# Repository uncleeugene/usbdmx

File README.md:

# usbdmx
Galvanically isolated clone of Enttec USB-DMX

Notice: "main" branch contains USB-B version of the board. In "usbc" branch there is USB-C version, but it is not done yet!

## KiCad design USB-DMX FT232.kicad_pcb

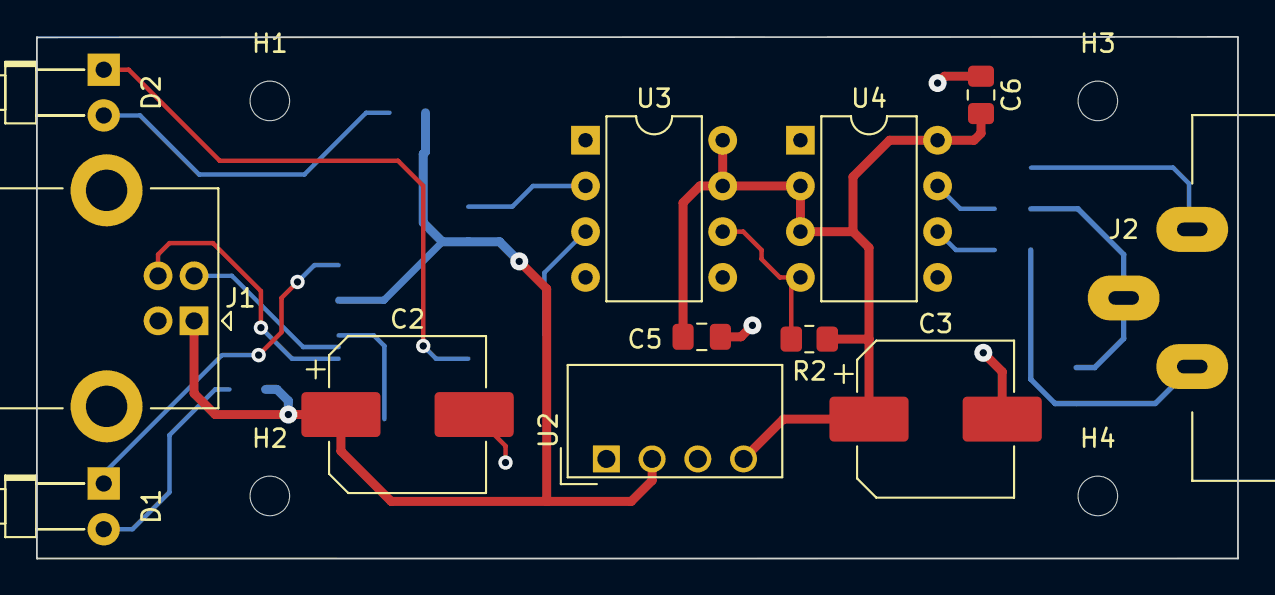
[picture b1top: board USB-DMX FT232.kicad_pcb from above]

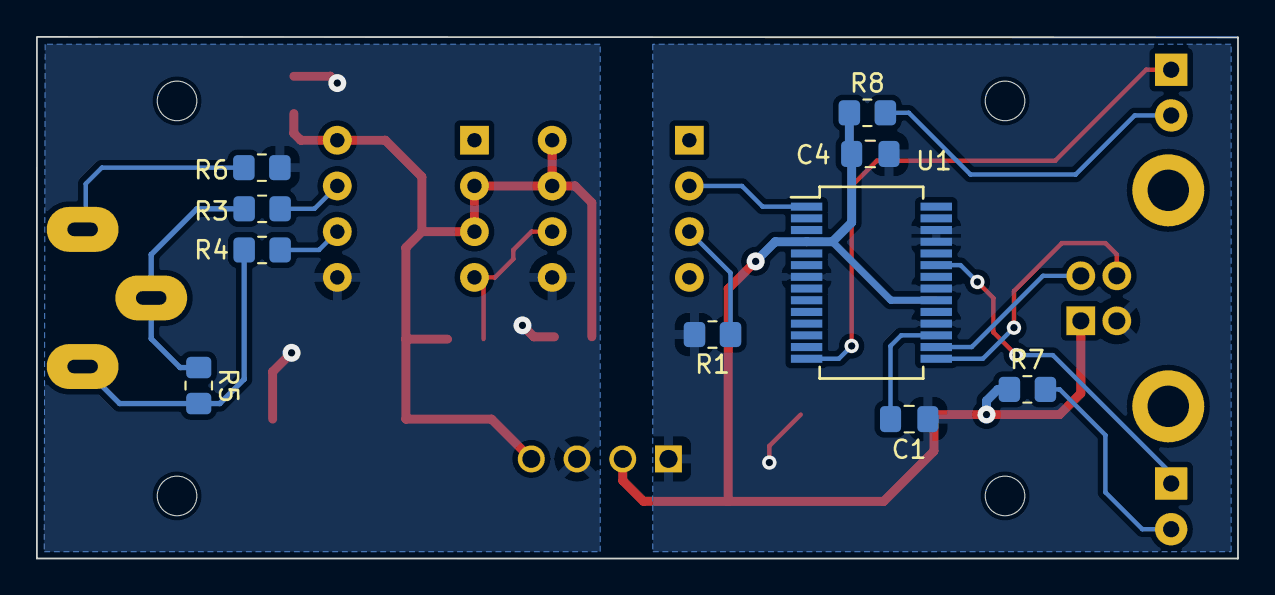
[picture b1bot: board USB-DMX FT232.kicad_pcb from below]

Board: 2 copper layers, 66.7 x 29.0 mm, 26 parts (10 on the bottom side), 19 nets.

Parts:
C1: 100nF; C_0805_2012Metric_Pad1.18x1.45mm_HandSolder
C2, C3: 100uF; CP_Elec_8x10.5
C4, C5, C6: 10nF; C_0805_2012Metric_Pad1.18x1.45mm_HandSolder
D1, D2: LED; LED_D1.8mm_W1.8mm_H2.4mm_Horizontal_O3.81mm_Z1.6mm
H1, H2, H3, H4: MountingHole_Pad; MountingHole_2.2mm_M2
J1: USB; USB_B_Lumberg_2411_02_Horizontal
J2: NC3MAFH-PH; XLR 3pin Female Angle
R1: 1K; R_0805_2012Metric_Pad1.20x1.40mm_HandSolder
R2: 10K; R_0805_2012Metric_Pad1.20x1.40mm_HandSolder
R3, R4, R6: 10; R_0805_2012Metric_Pad1.20x1.40mm_HandSolder
R5: 120; R_0805_2012Metric_Pad1.20x1.40mm_HandSolder
R7, R8: 220; R_0805_2012Metric_Pad1.20x1.40mm_HandSolder
U1: FT232RL; SSOP-28_5.3x10.2mm_P0.65mm
U2: TEA1-0505; Converter_DCDC_TRACO_TEA1-xxxx_THT
U3: 6N137; DIP-8_W7.62mm
U4: MAX485E; DIP-8_W7.62mm

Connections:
GND: C1.1, C2.2, C4.1, J1.4 (GND), R1.2, U1.7 (GND), U1.18 (GND), U1.21 (GND), U1.25 (AGND), U1.26 (TEST), U2.1 (-Vin)
GND2: C3.2, C5.1, C6.1, R6.2, U2.3 (-Vout), U3.5 (GND), U4.5 (GND)
unnamed: D1.2 (A), R7.2
unnamed: D1.1 (K), U1.23 (CBUS0)
unnamed: D2.2 (A), R8.2
unnamed: D2.1 (K), U1.14 (CBUS3)
unnamed: J1.3 (D+), U1.15 (USBD+)
unnamed: J1.2 (D-), U1.16 (USBD-)
unnamed: J2.1, R6.1
unnamed: J2.2, R4.2, R5.2
unnamed: J2.3, R3.2, R5.1
unnamed: C1.2, U1.17 (3V3OUT)
unnamed: U1.1 (TXD), U3.2 (A)
unnamed: R1.1, U3.3 (C)
unnamed: R2.2, U3.6 (VO), U4.4 (DI)
unnamed: R4.1, U4.6 (A)
unnamed: R3.1, U4.7 (B)
VCC: C2.1, C4.2, J1.1 (VBUS), R7.1, R8.1, U1.4 (VCCIO), U1.20 (VCC), U2.2 (+Vin)
VDD: C3.1, C5.2, C6.2, R2.1, U2.4 (+Vout), U3.7 (EN), U3.8 (VCC), U4.2 (~RE), U4.3 (DE), U4.8 (VCC)

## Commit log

2026-02-09 usbc version
